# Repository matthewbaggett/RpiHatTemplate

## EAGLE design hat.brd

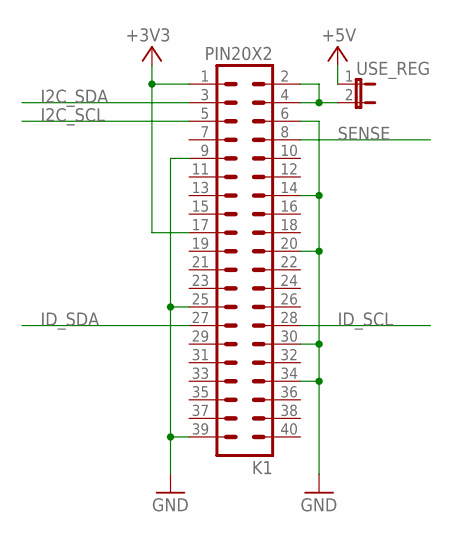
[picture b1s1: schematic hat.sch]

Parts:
K1: PIN20X2; PIN_20X2
USE_REG: JP1E; JP1

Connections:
+3V3: K1.1, K1.17
+5V: USE_REG.1
GND: K1.6, K1.9, K1.14, K1.20, K1.25, K1.30, K1.34, K1.39
I2C_SCL: K1.5
I2C_SDA: K1.3
ID_SCL: K1.28
ID_SDA: K1.27
unnamed: K1.2, K1.4, USE_REG.2
SENSE: K1.8

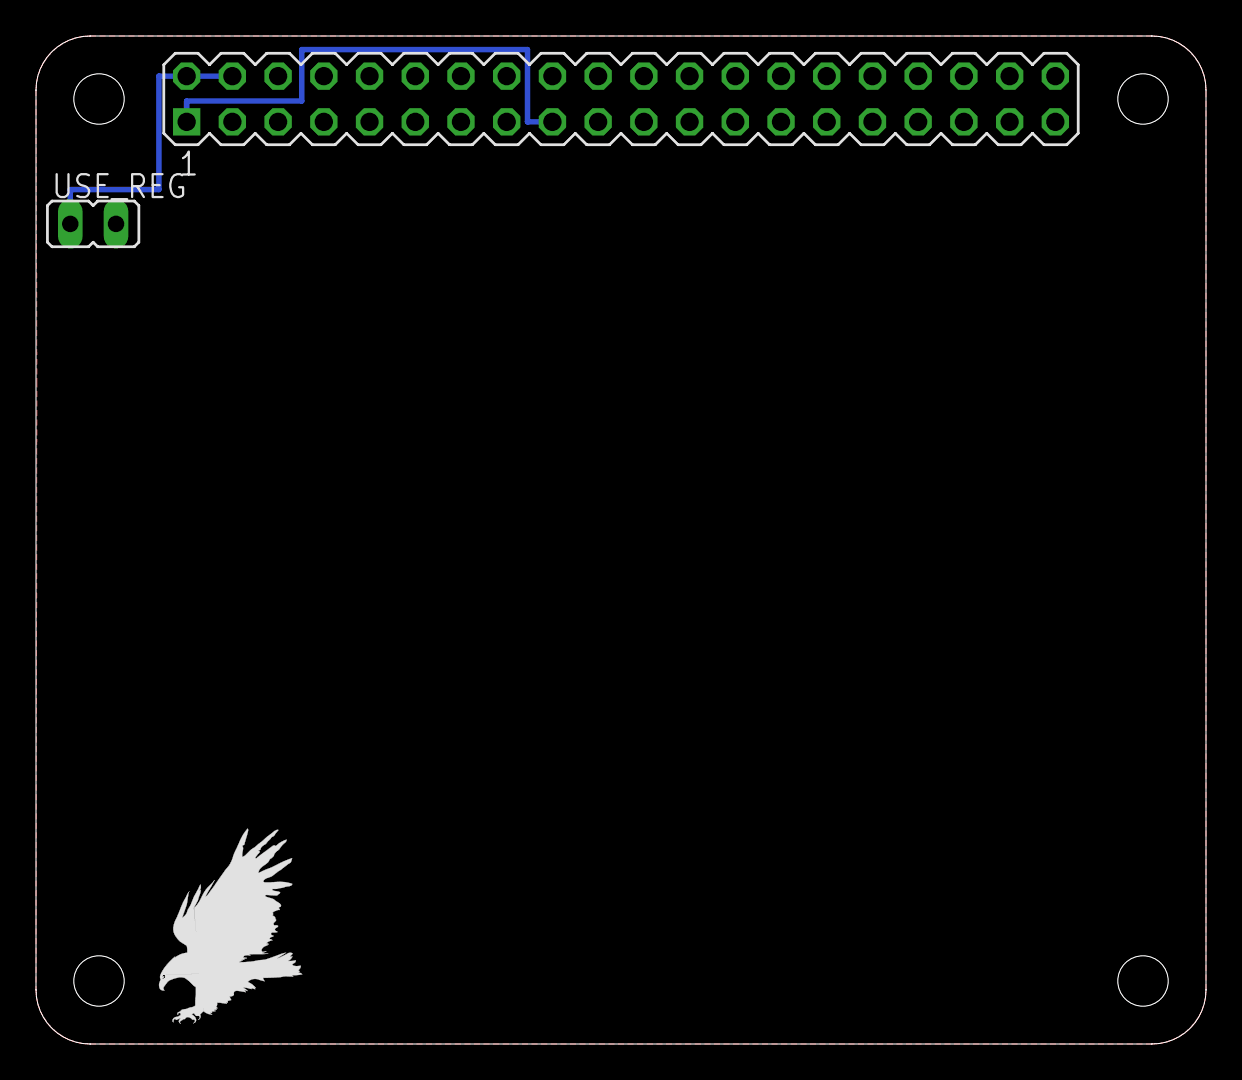
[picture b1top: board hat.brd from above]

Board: 2 copper layers, 65.0 x 56.0 mm, 3 parts (0 on the bottom side), 3 nets.

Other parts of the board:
U$1: EAGLE-PLC-8MM
